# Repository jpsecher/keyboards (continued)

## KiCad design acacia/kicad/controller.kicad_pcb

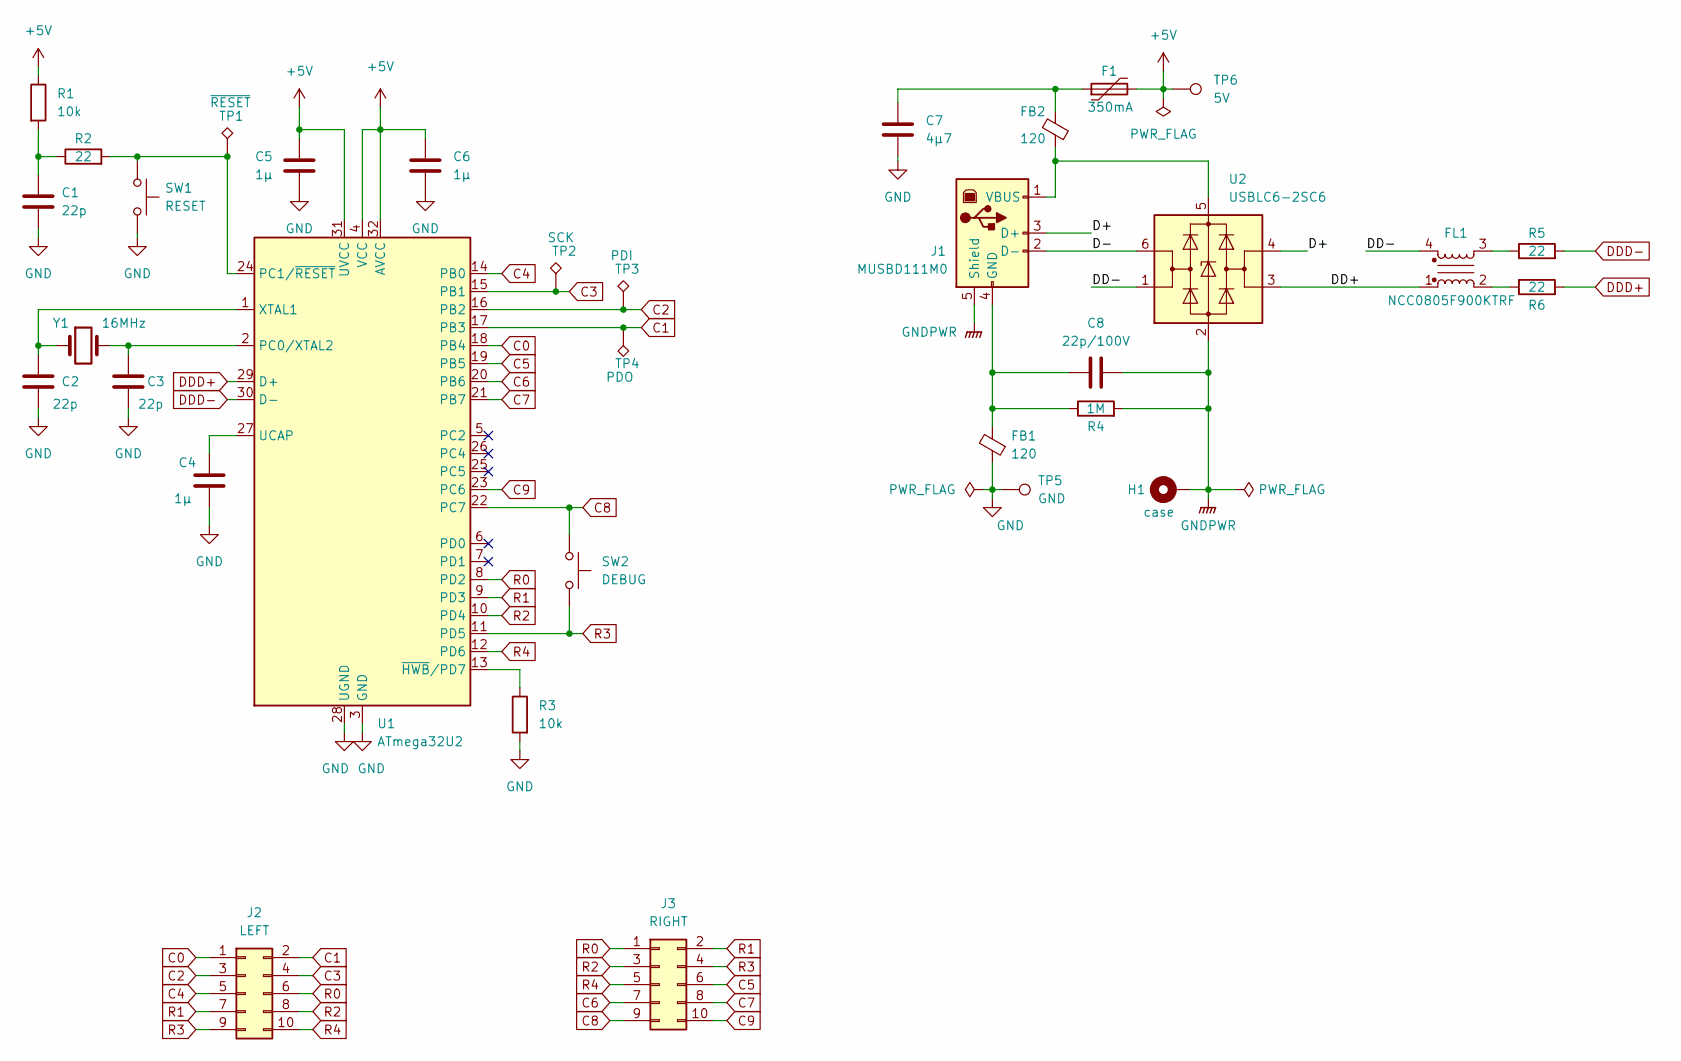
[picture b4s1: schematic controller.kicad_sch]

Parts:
C1, C2, C3: 22p; C_0805_2012Metric_Pad1.18x1.45mm_HandSolder
C4: 1µ; C_1206_3216Metric_Pad1.33x1.80mm_HandSolder
C5, C6: 1µ; C_0805_2012Metric_Pad1.18x1.45mm_HandSolder
C7: 4µ7; C_0805_2012Metric_Pad1.18x1.45mm_HandSolder
C8: 22p/100V; C_0805_2012Metric_Pad1.18x1.45mm_HandSolder
F1: 350mA; R_1210_3225Metric_Pad1.30x2.65mm_HandSolder
FB1, FB2: 120; R_0805_2012Metric_Pad1.20x1.40mm_HandSolder
FL1: NCC0805F900KTRF; L_CommonModeChoke_Coilcraft_0805USB
H1: case; MountingHole_3.2mm_M3_DIN965_Pad
J1: MUSBD111M0; AMPHENOL_MUSBD111M0
J2: LEFT; IDC-Header_2x05_P2.54mm_Horizontal
J3: RIGHT; IDC-Header_2x05_P2.54mm_Horizontal
R1, R3: 10k; R_0805_2012Metric_Pad1.20x1.40mm_HandSolder
R2, R5, R6: 22; R_0805_2012Metric_Pad1.20x1.40mm_HandSolder
R4: 1M; R_0805_2012Metric_Pad1.20x1.40mm_HandSolder
SW1: RESET; SW_SPST_EVQQ2
SW2: DEBUG; SW_SPST_EVQQ2
TP1: ~{RESET}; TestPoint_Pad_1.0x1.0mm
TP2: SCK; TestPoint_Pad_1.0x1.0mm
TP3: PDI; TestPoint_Pad_1.0x1.0mm
TP4: PDO; TestPoint_Pad_1.0x1.0mm
TP5: GND; TestPoint_Pad_1.0x1.0mm
TP6: 5V; TestPoint_Pad_1.0x1.0mm
U1: ATmega32U2; TQFP-32_7x7mm_P0.8mm
U2: USBLC6-2SC6; SOT-23-6
Y1: 16MHz; Crystal_SMD_HC49-SD

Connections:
+5V: C5.1, C6.1, F1.2, R1.1, TP6.1, U1.4 (VCC), U1.31 (UVCC), U1.32 (AVCC)
/D+: J1.3 (D+), U2.4 (I/O2)
/D-: J1.2 (D-), U2.6 (I/O1)
/DD+: FL1.1, U2.3 (I/O2)
/DD-: FL1.4, U2.1 (I/O1)
C0: J2.1, U1.18 (PB4)
C1: J2.2, TP4.1, U1.17 (PB3)
C2: J2.3, TP3.1, U1.16 (PB2)
C3: J2.4, TP2.1, U1.15 (PB1)
C4: J2.5, U1.14 (PB0)
C5: J3.6, U1.19 (PB5)
C6: J3.7, U1.20 (PB6)
C7: J3.8, U1.21 (PB7)
C8: J3.9, SW2.1, U1.22 (PC7)
C9: J3.10, U1.23 (PC6)
DDD+: R6.2, U1.29 (D+)
DDD-: R5.2, U1.30 (D-)
GND: C1.2, C2.2, C3.2, C4.2, C5.2, C6.2, C7.2, FB1.1, R3.2, SW1.2, TP5.1, U1.3 (GND), U1.28 (UGND)
GNDPWR: C8.1, H1.1, J1.5 (Shield), R4.2, U2.2 (GND)
unnamed: C1.1, R1.2, R2.1
unnamed: C2.1, U1.1 (XTAL1), Y1.1
unnamed: C3.1, U1.2 (PC0/XTAL2), Y1.2
unnamed: C4.1, U1.27 (UCAP)
unnamed: C7.1, F1.1, FB2.1
unnamed: C8.2, FB1.2, J1.4 (GND), R4.1
unnamed: FB2.2, J1.1 (VBUS), U2.5 (VBUS)
unnamed: FL1.2, R6.1
unnamed: FL1.3, R5.1
unnamed: R2.2, SW1.1, TP1.1, U1.24 (PC1/~RESET)
unnamed: R3.1, U1.13 (~HWB/PD7)
R0: J2.6, J3.1, U1.8 (PD2)
R1: J2.7, J3.2, U1.9 (PD3)
R2: J2.8, J3.3, U1.10 (PD4)
R3: J2.9, J3.4, SW2.2, U1.11 (PD5)
R4: J2.10, J3.5, U1.12 (PD6)

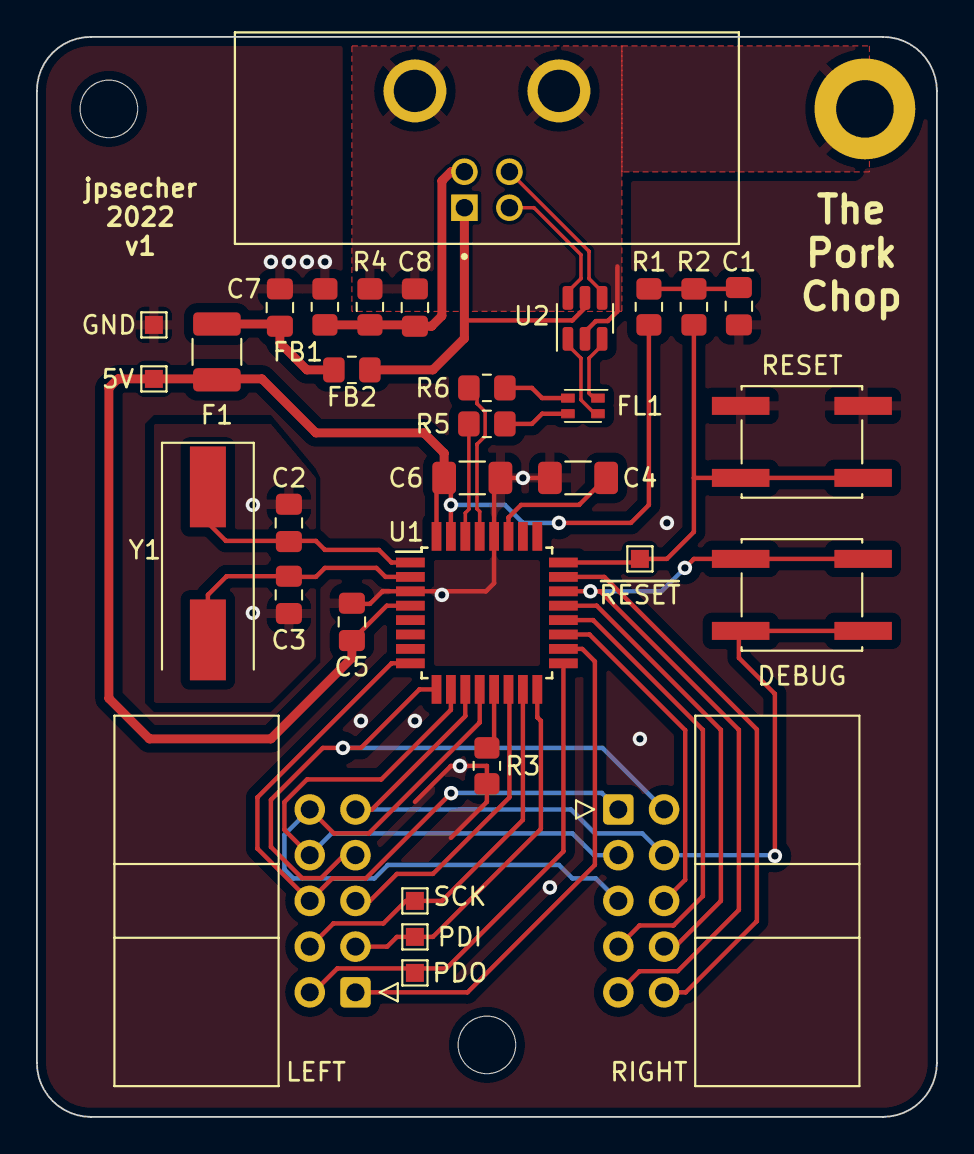
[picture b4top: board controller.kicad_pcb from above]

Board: 2 copper layers, 50.0 x 60.0 mm, 33 parts (0 on the bottom side), 35 nets.

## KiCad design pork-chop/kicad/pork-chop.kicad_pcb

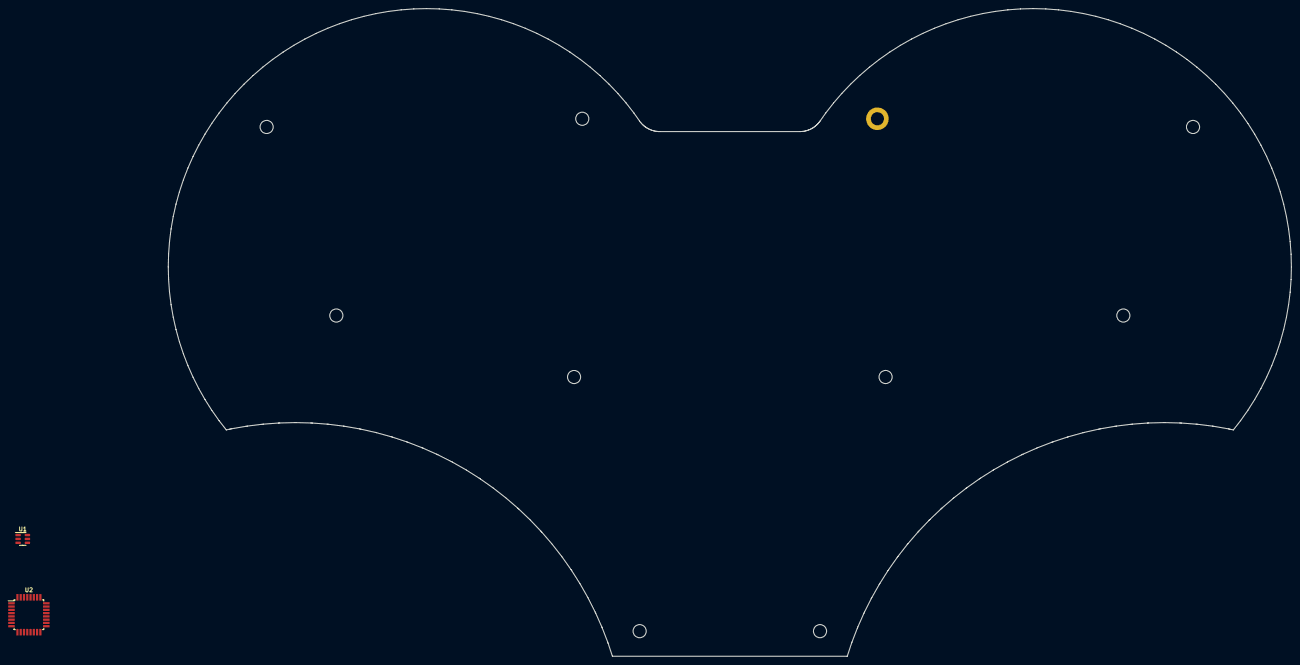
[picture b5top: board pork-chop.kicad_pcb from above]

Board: 2 copper layers, 274.0 x 158.0 mm, 12 parts (0 on the bottom side), 3 nets, no tracks yet.

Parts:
H1: case; MountingHole_3.2mm_M3_ISO14580_Pad
H2, H3, H4, H5, H6, H7, H8, H9, H10: MountingHole; MountingHole_3.2mm_M3
U1: USBLC6-2SC6; SOT-23-6
U2: ATmega32U2-A; TQFP-32_7x7mm_P0.8mm

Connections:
+5V: U2.4 (VCC), U2.31 (UVCC), U2.32 (AVCC)
GND: U2.3 (GND), U2.28 (UGND)
GNDPWR: H1.1, U1.2 (GND)

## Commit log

2022-11-05 License
2022-11-05 Goals
2022-11-05 Fiddling with SVG
2022-11-05 Thumbs
2022-11-05 More thumb, less pinky
2022-11-09 smalller verison
2022-11-11 Thumb keys
2022-11-11 small font
2022-11-11 Smaller text
2022-11-12 Generate preliminary layout and map
2022-11-12 More angles
2022-11-12 Rename
2022-11-12 Hidden config buttons
2022-11-12 Keymap
2022-11-12 Limit wideness
2022-11-13 layout 4*5_4
2022-11-13 Big extra key
2022-11-13 Minion V1
2022-11-13 Optional fourth key
2022-11-13 6x10 matrix
2022-11-13 Optimise layers
2022-11-14 Switch Tab/Enter
2022-11-14 Swap thumbs
2022-11-14 Documentation
2022-11-14 WIP: schematic
2022-11-15 Minus on layer 0, quotes on prime position layer 2
2022-11-15 schematic and footprints from ai03
2022-11-17 Schematic for full keyboard
2022-11-17 Earth connection on the other side of filter
2022-11-17 Allow for Alt-Tab
2022-11-21 More spead
2022-11-23 OpenSCAD plate
2022-11-23 Slick contour
2022-11-25 Top tabs
2022-11-25 both sides
2022-11-27 Bottom skirt
2022-11-27 Updated spacing based on prototype
2022-11-27 Better feet
2022-11-28 Using Elephant42 as basis
2022-11-29 40 keys
2022-11-29 Complete board
2022-11-30 Routing
2022-12-01 swap gui/ctrl
2022-12-03 Silk screen
2022-12-03 cable hole
2022-12-04 move programming pads
2022-12-11 Newest layout
2022-12-12 remap
2022-12-13 More one-shot keys
2022-12-13 thinner plate & room for connector
2022-12-13 use actual cap sizes
2022-12-13 generic key size
2022-12-13 2D projection for export to SVG
2022-12-14 better minus
2022-12-14 full board wip
2022-12-15 layout with 1.5u & 1.25u
2022-12-15 outlines
2022-12-17 pcb with standoffs
2022-12-18 before reorder
2022-12-18 rearrange
2022-12-19 keys layed out
2022-12-20 keys routed
2022-12-21 Enter/tab on base layer
2022-12-21 Layer swap & normal numbers
2022-12-21 routing done
2022-12-22 quot on main layer
2022-12-23 pcb finished
2022-12-23 Layers on different hands
2022-12-25 least amount of shuffling around
2022-12-26 plate only
2022-12-28 first attempt on Via spec
2022-12-28 Via spec adjusted
2022-12-28 Use column X row as labels so KLE export can be directly imported in Via
2023-01-04 swap shift alt
2023-01-07 Cleanup
2023-01-07 pictures
2023-01-07 Links
2023-01-07 Explanation of the layers
2023-01-07 Improvements
2023-01-09 swap layers to enable right-hand trackball operation
2023-01-11 rework after use
2023-01-15 minimak
2023-01-15 Minimak-4 layout
2023-01-16 WIP: Acadia
2023-01-16 Small finger adjustment
2023-01-20 Top row modifiers
2023-01-20 Lower row mods
2023-01-21 Modifiers on lower home row
2023-01-22 Revert to T style cursor keys
2023-01-23 Slash instead of colon
2023-01-25 Layer Lock
2023-01-25 Switch deletion and shift
2023-01-25 GESC
2023-01-26 Status LED
2023-02-11 Better lock, Del on Shift BS
2023-02-12 Shift Alt on extra key
2023-02-13 Alternatives
2023-02-13 Swap Tab and Backspace
2023-02-23 Swap D, F, T and regular enter
2023-03-24 Navigation on right hand, edit on left
2023-03-26 vi cursors & copy/paste that works everywhere
2023-03-26 tilde
2023-03-27 V2, yet another key gone
2023-03-28 Better symbols on Nav and Sublime duplicate cursor
2023-03-29 minus swap
2023-03-29 double tap for CW
2023-04-03 More short cuts
2023-04-04 Sublime keys
2023-04-05 Swap O and Y
2023-04-06 Drop lower thumbs
2023-04-06 Diff to QWERTY
2023-04-06 Nope, swap back O and Y, which gives higher score and is closer to QWERTY
2023-04-07 Starting V2 layout
2023-04-09 V2 PCB started
2023-04-10 WIP: v2 board
2023-04-22 Double tap layers to lock
2023-04-24 Base on same key on all layers
2023-04-27 Cursor allignment
2023-04-27 Alpha layer on Esc
2023-04-29 New USB connector
2023-05-14 Symbols rearrange
2023-05-19 Mouse on Nav, infrequent symbols on Func
2023-05-23 Swap aux symbols
2023-05-31 Swap inequality symbols
2023-06-19 Swap zero, minus & underscore
2023-07-27 Don't lock symbol layer
2023-09-01 USB cutout only half
2023-09-15 Allign CTLx with actual keys
2023-10-01 qwerty layout
2023-10-02 qwerty
2023-10-16 Shift lower-right row
2023-10-17 Symbols
2023-10-18 before reordering
2023-10-18 leds
2023-10-18 V2 gerber
2023-12-04 Swap Nav & AGr, clear Esc
2024-01-03 Swap AltGr and Func
2024-01-23 Swap slash, backslash, comma
2024-01-23 Adjust key position to better fit actual layout
2024-01-28 Cut out for flat cable
2024-01-29 mouse wheel
2024-03-15 Eliminate two more keys
2024-03-28 BAV70U quad diode
2024-03-30 Switch round Esc/Tab & one-shot alpha in Navi
2024-04-10 Enter back on alpha
2024-07-24 Starting v3: Thrice
2024-08-17 Homerow mods
2024-08-19 Fixes
2024-08-20 Rework
2024-08-20 Alternative Mods
2024-09-11 Alternate layout
2024-09-13 slash
2024-09-14 testing delimiter together
2024-09-30 reorder minus
2024-11-16 cursor layout
2024-11-19 cursor v4
2024-11-21 mtgap cursor mod
2024-11-26 Acacia transferred to Voyager
    clone https://github.com/zsa/qmk_firmware/
    cp to keyboards/zsa/voyager/keymaps/acacia and run
    make zsa/voyager:acacia:flash
2024-11-26 move 0
2024-12-01 Backup of qmk stuff
2024-12-07 final choc cover cap
2024-12-08 Choc v1 covers
2025-01-15 Layout 36
2025-01-15 symbol reshuffle
2025-02-09 quotes between parantheses & one-shot meh + hyper
2025-06-01 oneshot layers
